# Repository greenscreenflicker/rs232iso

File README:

For a first orientation read the datasheet.
If you want to reproduce the design, please go to the kicad folder.
The KiCAD Design files are available here and the gerber files for production.

For 3D printing the case, the design files are in the folder 3D Case.

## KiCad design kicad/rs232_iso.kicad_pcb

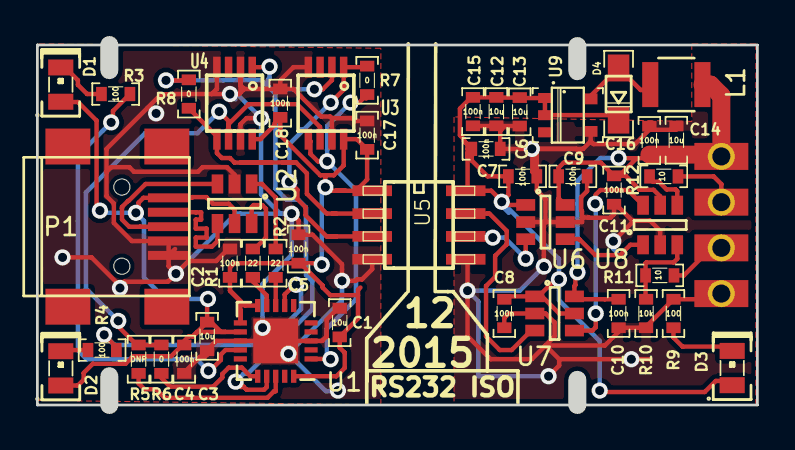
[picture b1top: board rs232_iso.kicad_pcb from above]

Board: 2 copper layers, 39.1 x 20.0 mm, 46 parts (0 on the bottom side), 33 nets.

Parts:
C1, C3, C12, C13, C14: 10u; SMD-C-0603
C2, C4, C5, C6, C7, C8, C9, C10, C11, C15, C16, C17, C18: 100n; SMD-C-0603
D1, D2, D3: LED; LED0805
D4: PMEG3010; SOD323-W
L1: 47u; R_1210
P1: EDAC-690-005-299-143; USB_Mini-B
P2: CONN_01X04; ISP_MSP430_2.54
R1, R2: 22; SMD-R-0603
R3, R4, R9: 100; SMD-R-0603
R5: DNP; SMD-R-0603
R6, R7, R8: 0; SMD-R-0603
R10: 10k; SMD-R-0603
R11, R12: 10; SMD-R-0603
U1: FT231XQ; QFN-20-1EP_4x4mm_Pitch0.5mm
U2, U8: TPD2S017; SOT-23-6
U3, U4: DNP(74LVC2G157); ssop-8
U5: Si8621BB; SO08
U6, U7: SN74LVC1T45DBV; SOT-23-6
U9: NCP1402SN50T1G; SOT23-5

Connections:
3V3: C1.1, C2.1, C5.1, C17.2, C18.2, U1.10, U1.11, U1.20, U3.8, U4.8, U5.1
+5V: C3.1, C4.1, D1.2, D2.2, P1.1, U1.12, U2.5
DIR: R5.1, R6.1, U3.6, U4.6
GND: C1.2, C2.2, C3.2, C4.2, C5.2, C17.1, C18.1, P1.4, P1.5, U1.3, U1.13, U1.21, U2.2, U3.4, U3.7, U4.2, U4.4, U4.7, U5.4
GNDdevice: C6.1, C7.2, C8.2, C9.2, C10.2, C11.1, C12.2, C13.2, C14.2, C15.2, C16.2, P2.4, R9.2, R10.2, U5.5, U6.2, U6.5, U7.2, U8.2, U9.4
unnamed: D1.1, R3.1
unnamed: D2.1, R4.1
unnamed: D3.1, R9.1
unnamed: D4.2, L1.2, U9.5
unnamed: P1.2, U2.4
unnamed: P1.3, U2.3
unnamed: P2.2, R12.1
unnamed: P2.3, R11.1
unnamed: R1.1, U1.9
unnamed: R2.1, U1.8
unnamed: R5.2, U1.18
unnamed: R6.2, U1.16
unnamed: R7.1, U3.1, U5.3
unnamed: R7.2, U1.1, U3.5
unnamed: R8.1, U4.5, U5.2
unnamed: U5.6, U6.3
unnamed: U5.7, U7.3
unnamed: U6.4, U8.1
unnamed: U7.4, U8.6
RXLED: R3.2, U1.14
RXdevice: R10.1, R11.2, U8.3
TXFTDI: R8.2, U1.17, U3.2, U4.1
TXLED: R4.2, U1.7
TXdevice: R12.2, U8.4
USBD+: R2.2, U2.1
USBD-: R1.2, U2.6
Vdevice: C9.1, C10.1, C11.2, C14.1, C16.1, L1.1, P2.1, U6.6, U7.6, U8.5
Vout: C6.2, C7.1, C8.1, C12.1, C13.1, C15.1, D3.2, D4.1, U5.8, U6.1, U7.1, U7.5, U9.1, U9.2

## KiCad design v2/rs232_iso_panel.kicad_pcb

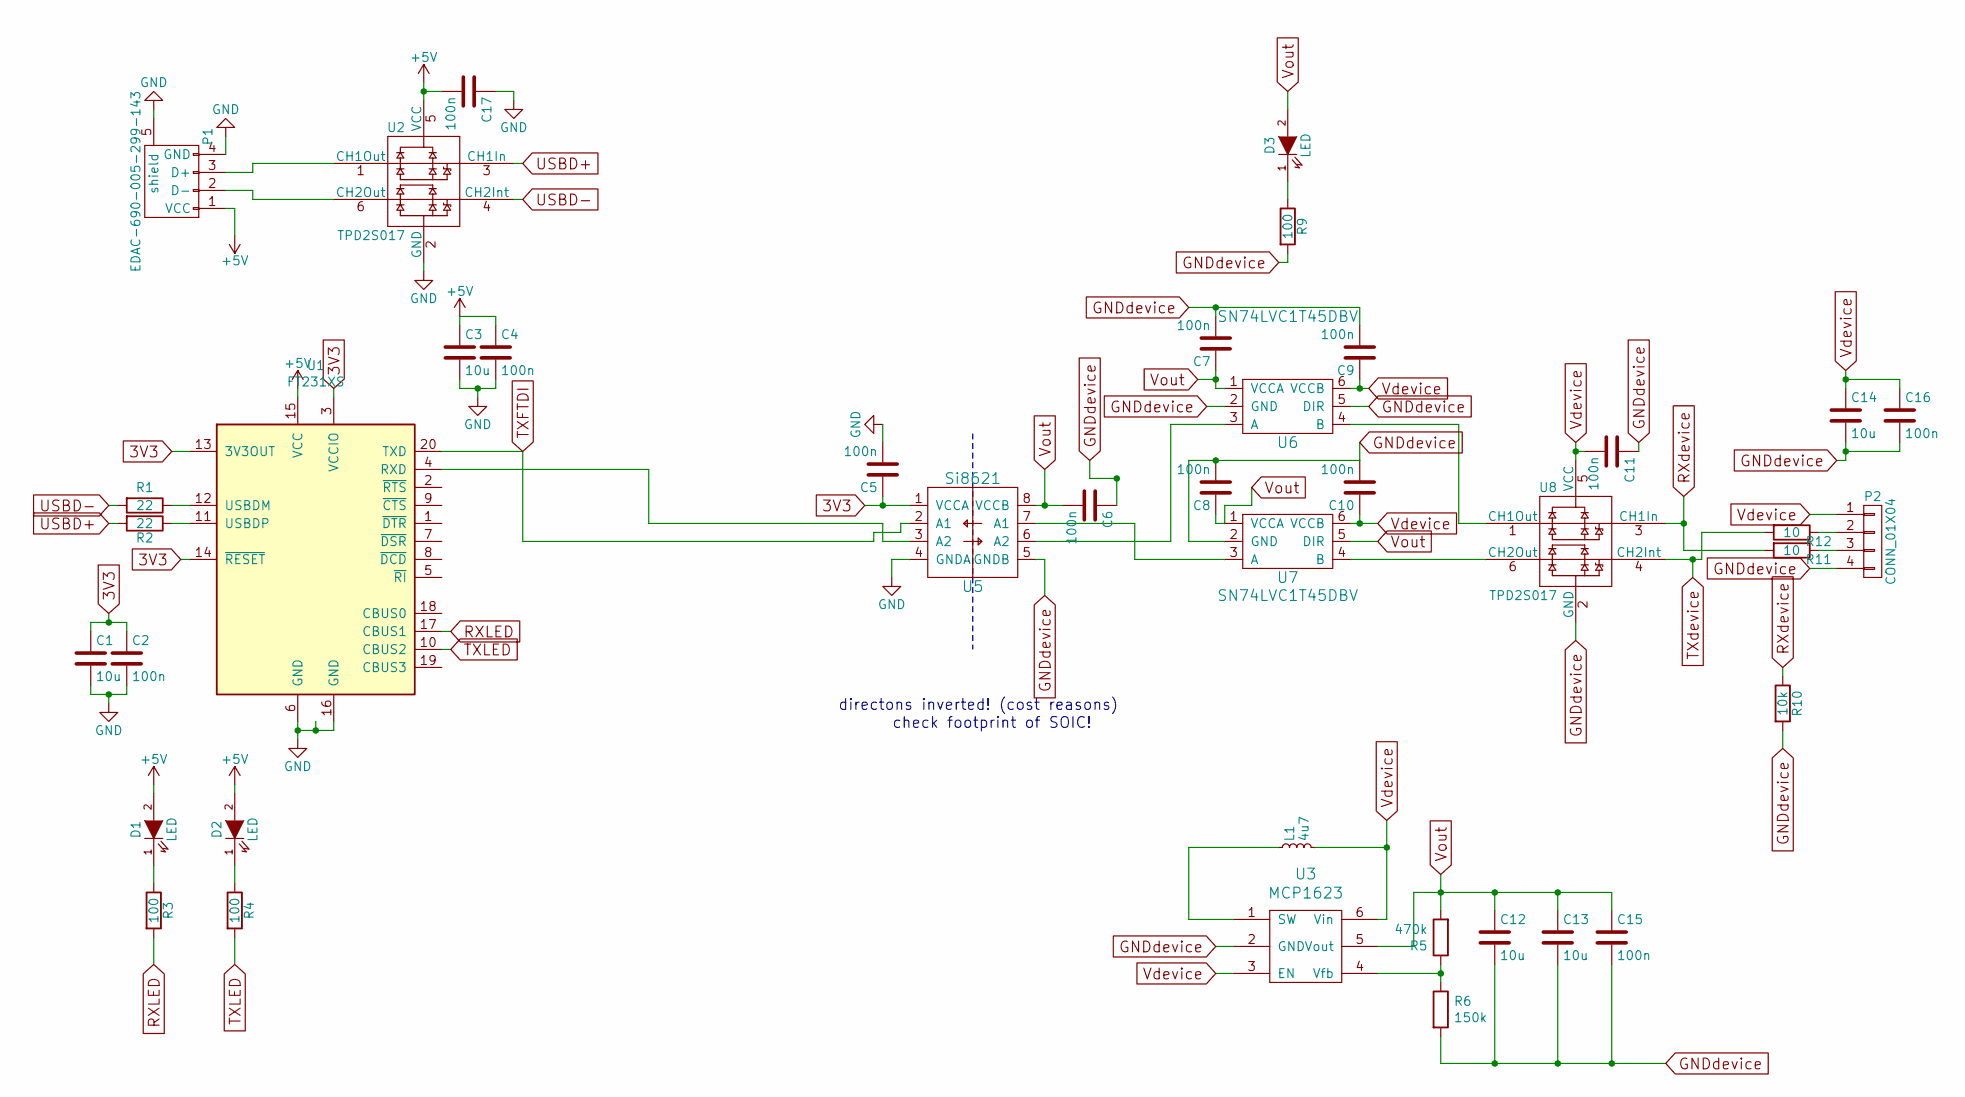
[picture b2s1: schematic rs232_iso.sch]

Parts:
C1, C3, C12, C13, C14: 10u; SMD-C-0603
C2, C4, C5, C6, C7, C8, C9, C10, C11, C15, C16, C17: 100n; SMD-C-0603
D1, D2, D3: LED; LED0805
L1: 4u7; R_1210
P1: EDAC-690-005-299-143; USB_Mini-B
P2: CONN_01X04; ISP_MSP430_2.54-2
R1, R2: 22; SMD-R-0603
R3, R4, R9: 100; SMD-R-0603
R5: 470k; SMD-R-0603
R6: 150k; SMD-R-0603
R10: 10k; SMD-R-0603
R11, R12: 10; SMD-R-0603
U1: FT231XS; SSOP-20_5.3x7.2mm_Pitch0.65mm
U2, U8: TPD2S017; SOT-23-6
U3: MCP1623; SOT-23-6
U5: Si8621; SOIC-8_3.9x4.9mm_Pitch1.27mm
U6, U7: SN74LVC1T45DBV; SOT-23-6

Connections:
3V3: C1.1, C2.1, C5.1, U1.3 (VCCIO), U1.13 (3V3OUT), U1.14 (~RESET), U5.1 (VCCA)
+5V: C3.1, C4.1, C17.2, D1.2 (A), D2.2 (A), P1.1 (VCC), U1.15 (VCC), U2.5 (VCC)
GND: C1.2, C2.2, C3.2, C4.2, C5.2, C17.1, P1.4 (GND), P1.5 (shield), U1.6 (GND), U1.16 (GND), U2.2 (GND), U5.4 (GNDA)
GNDdevice: C6.1, C7.2, C8.2, C9.2, C10.2, C11.1, C12.2, C13.2, C14.2, C15.2, C16.2, P2.4, R6.2, R9.2, R10.2, U3.2 (GND), U5.5 (GNDB), U6.2 (GND), U6.5 (DIR), U7.2 (GND), U8.2 (GND)
unnamed: D1.1 (K), R3.1
unnamed: D2.1 (K), R4.1
unnamed: D3.1 (K), R9.1
unnamed: L1.1, U3.1 (SW)
unnamed: P1.2 (D-), U2.6 (CH2Out)
unnamed: P1.3 (D+), U2.1 (CH1Out)
unnamed: P2.2, R12.1
unnamed: P2.3, R11.1
unnamed: R1.1, U1.12 (USBDM)
unnamed: R2.1, U1.11 (USBDP)
unnamed: R5.1, R6.1, U3.4 (Vfb)
unnamed: U1.4 (RXD), U5.3 (A2)
unnamed: U5.6 (A2), U6.3 (A)
unnamed: U5.7 (A1), U7.3 (A)
unnamed: U6.4 (B), U8.1 (CH1Out)
unnamed: U7.4 (B), U8.6 (CH2Out)
RXLED: R3.2, U1.17 (CBUS1)
RXdevice: R10.1, R11.2, U8.3 (CH1In)
TXFTDI: U1.20 (TXD), U5.2 (A1)
TXLED: R4.2, U1.10 (CBUS2)
TXdevice: R12.2, U8.4 (CH2Int)
USBD+: R2.2, U2.3 (CH1In)
USBD-: R1.2, U2.4 (CH2Int)
Vdevice: C9.1, C10.1, C11.2, C14.1, C16.1, L1.2, P2.1, U3.3 (EN), U3.6 (Vin), U6.6 (VCCB), U7.6 (VCCB), U8.5 (VCC)
Vout: C6.2, C7.1, C8.1, C12.1, C13.1, C15.1, D3.2 (A), R5.2, U3.5 (Vout), U5.8 (VCCB), U6.1 (VCCA), U7.1 (VCCA), U7.5 (DIR)

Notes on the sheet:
check footprint of SOIC!
directons inverted! (cost reasons)

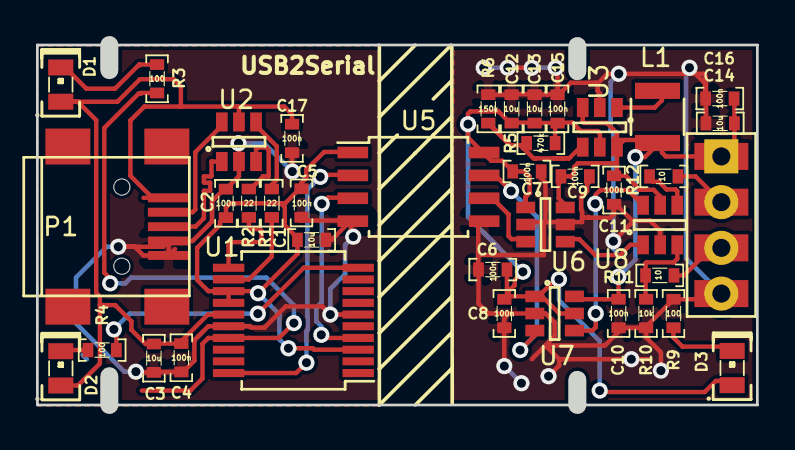
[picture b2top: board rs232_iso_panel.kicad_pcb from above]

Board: 2 copper layers, 39.1 x 20.0 mm, 40 parts (0 on the bottom side), 29 nets.

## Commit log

2016-02-22 Removed saved files
2016-02-22 removed backup files
2016-02-22 removed autosave files
2016-07-28 Added v2
2016-07-28 Added assembly files
